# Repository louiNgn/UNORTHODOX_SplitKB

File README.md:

# UNORTHOD0X SPLIT KEYBOARD 
## a "re-staggered" split ortholinear keyboard in between a 65% and a 75% keyboard utilizing usb-c interconnect

A cursed keyboard design that appreciates well-tuned stabilizers and keycap label compatibility while giving a bit of a damn about ergonomics and the well-being of your hands was the reason why this project was created. 

FIRMWARE IS TO BE ADDED ONCE I GET MY HANDS ON THE KEYBOARD, AS I DO NOT HAVE EXPERIENCE WITH DEVVING PI PICO INTERCONNECT!

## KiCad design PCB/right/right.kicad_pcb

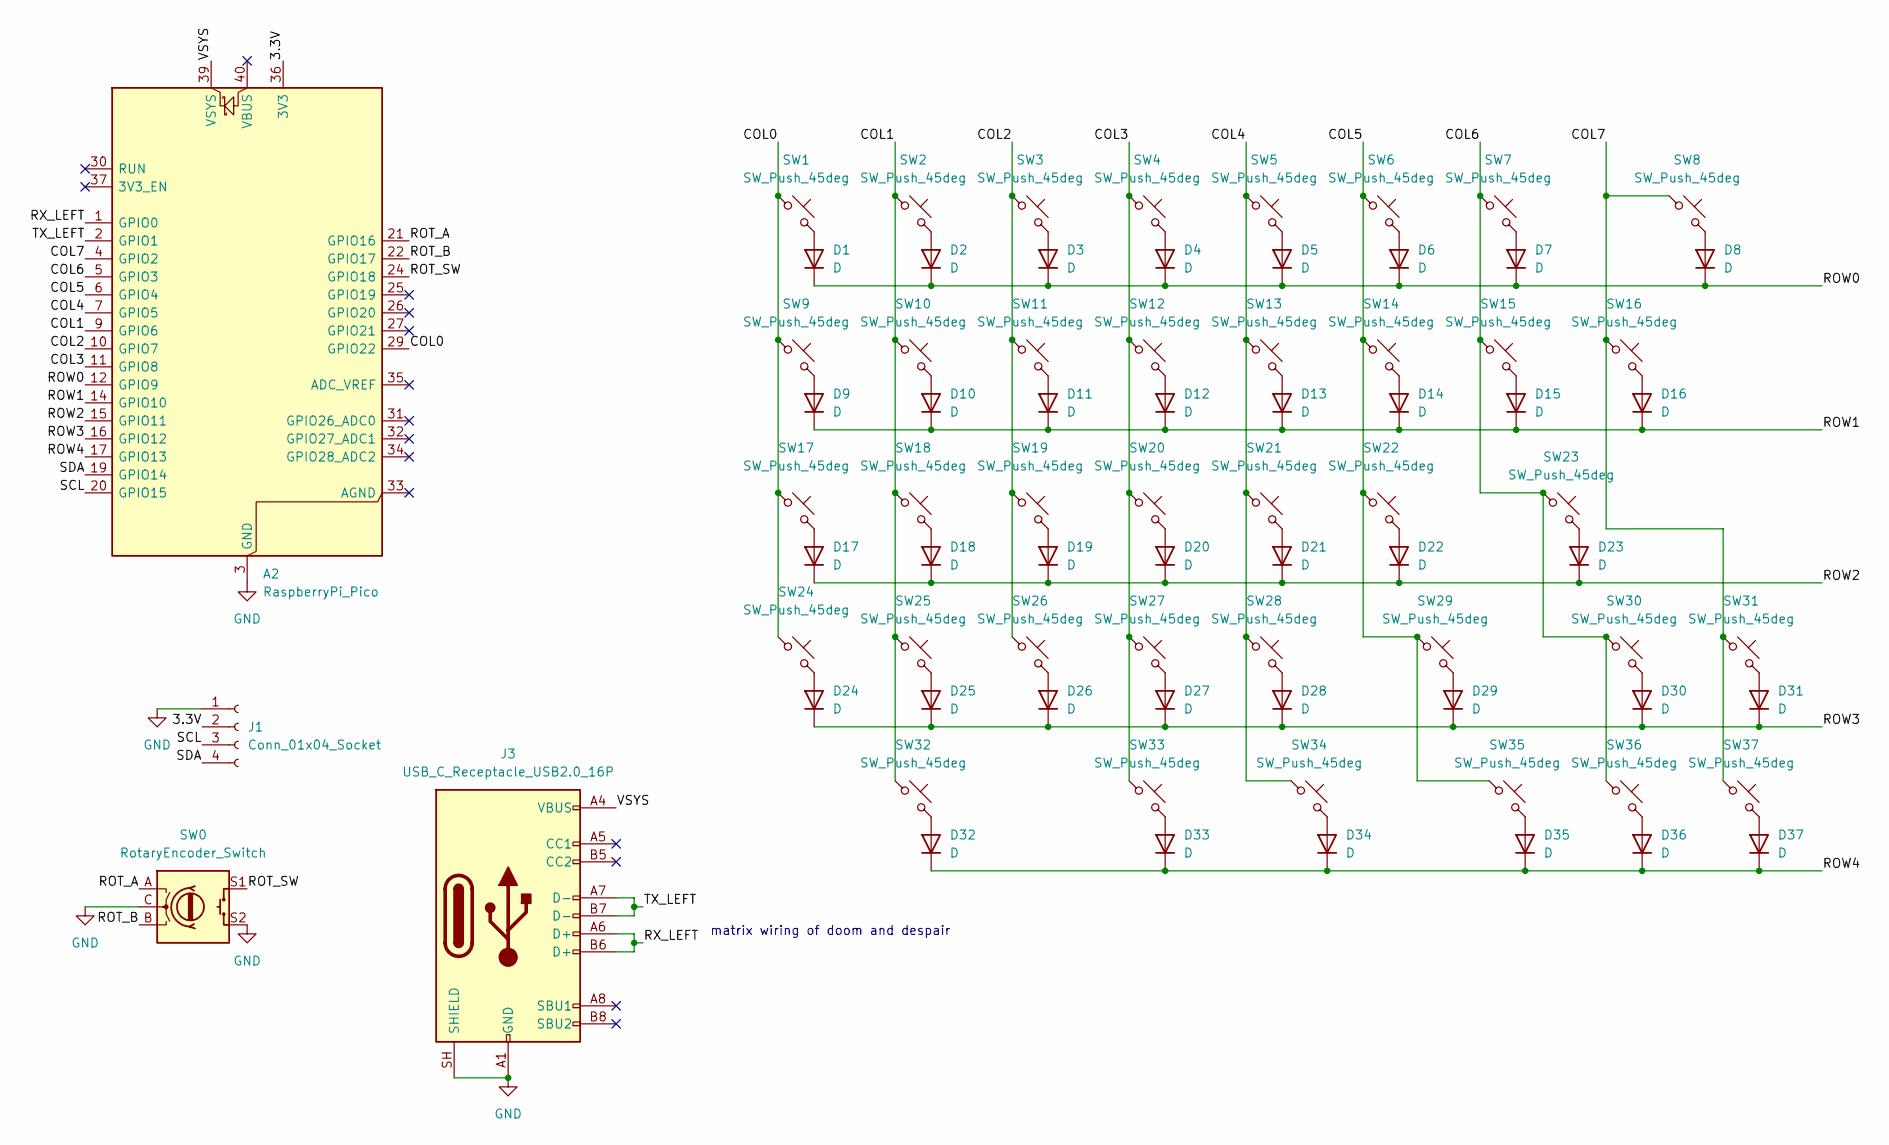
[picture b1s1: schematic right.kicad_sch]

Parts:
A2: RaspberryPi_Pico; RaspberryPi_Pico_Common_THT
D1, D2, D3, D4, D5, D6, D7, D8, D9, D10, D11, D12, D13, D14, D15, D16, D17, D18, D19, D20, D21, D22, D23, D24, D25, D26, D27, D28, D29, D30, D31, D32, D33, D34, D35, D36, D37: D; D_SOD-123
J1: Conn_01x04_Socket; ER_OLEDM0.91_1x-I2C
J3: USB_C_Receptacle_USB2.0_16P; USB_C_Receptacle_HCTL_HC-TYPE-C-16P-01A
SW0: RotaryEncoder_Switch; ROT_Alps_EC11E-Switch
SW1, SW2, SW3, SW4, SW5, SW6, SW7, SW9, SW10, SW11, SW12, SW13, SW14, SW15, SW17, SW18, SW19, SW20, SW21, SW22, SW24, SW25, SW26, SW27, SW28, SW30, SW31, SW35, SW36, SW37: SW_Push_45deg; SW_Hotswap_Kailh_MX_Plated_1.00u
SW8, SW16: SW_Push_45deg; SW_Hotswap_Kailh_MX_Plated_2.00u
SW23, SW32: SW_Push_45deg; SW_Hotswap_Kailh_MX_Plated_2.75u
SW29: SW_Push_45deg; SW_Hotswap_Kailh_MX_Plated_2.25u
SW33, SW34: SW_Push_45deg; SW_Hotswap_Kailh_MX_Plated_1.50u

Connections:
/3.3V: A2.36 (3V3), J1.2
/COL0: A2.29 (GPIO22), SW1.1, SW9.1, SW17.1, SW24.1
/COL1: A2.9 (GPIO6), SW2.1, SW10.1, SW18.1, SW25.1, SW32.1
/COL2: A2.10 (GPIO7), SW3.1, SW11.1, SW19.1, SW26.1
/COL3: A2.11 (GPIO8), SW4.1, SW12.1, SW20.1, SW27.1, SW33.1
/COL4: A2.7 (GPIO5), SW5.1, SW13.1, SW21.1, SW28.1, SW34.1
/COL5: A2.6 (GPIO4), SW6.1, SW14.1, SW22.1, SW29.1, SW35.1
/COL6: A2.5 (GPIO3), SW7.1, SW15.1, SW23.1, SW30.1, SW36.1
/COL7: A2.4 (GPIO2), SW8.1, SW16.1, SW31.1, SW37.1
/ROT_A: A2.21 (GPIO16), SW0.A
/ROT_B: A2.22 (GPIO17), SW0.B
/ROT_SW: A2.24 (GPIO18), SW0.S1
/ROW0: A2.12 (GPIO9), D1.1 (K), D2.1 (K), D3.1 (K), D4.1 (K), D5.1 (K), D6.1 (K), D7.1 (K), D8.1 (K)
/ROW1: A2.14 (GPIO10), D9.1 (K), D10.1 (K), D11.1 (K), D12.1 (K), D13.1 (K), D14.1 (K), D15.1 (K), D16.1 (K)
/ROW2: A2.15 (GPIO11), D17.1 (K), D18.1 (K), D19.1 (K), D20.1 (K), D21.1 (K), D22.1 (K), D23.1 (K)
/ROW3: A2.16 (GPIO12), D24.1 (K), D25.1 (K), D26.1 (K), D27.1 (K), D28.1 (K), D29.1 (K), D30.1 (K), D31.1 (K)
/ROW4: A2.17 (GPIO13), D32.1 (K), D33.1 (K), D34.1 (K), D35.1 (K), D36.1 (K), D37.1 (K)
/RX_LEFT: A2.1 (GPIO0), J3.A6 (D+), J3.B6 (D+)
/SCL: A2.20 (GPIO15), J1.3
/SDA: A2.19 (GPIO14), J1.4
/TX_LEFT: A2.2 (GPIO1), J3.A7 (D-), J3.B7 (D-)
/VSYS: A2.39 (VSYS), J3.A4 (VBUS), J3.A9 (VBUS), J3.B4 (VBUS), J3.B9 (VBUS)
GND: A2.3 (GND), A2.8 (GND), A2.13 (GND), A2.18 (GND), A2.23 (GND), A2.28 (GND), A2.38 (GND), J1.1, J3.A1 (GND), J3.A12 (GND), J3.B1 (GND), J3.B12 (GND), J3.SH (SHIELD), SW0.C, SW0.S2
unnamed: D1.2 (A), SW1.2
unnamed: D2.2 (A), SW2.2
unnamed: D3.2 (A), SW3.2
unnamed: D4.2 (A), SW4.2
unnamed: D5.2 (A), SW5.2
unnamed: D6.2 (A), SW6.2
unnamed: D7.2 (A), SW7.2
unnamed: D8.2 (A), SW8.2
unnamed: D9.2 (A), SW9.2
unnamed: D10.2 (A), SW10.2
unnamed: D11.2 (A), SW11.2
unnamed: D12.2 (A), SW12.2
unnamed: D13.2 (A), SW13.2
unnamed: D14.2 (A), SW14.2
unnamed: D15.2 (A), SW15.2
unnamed: D16.2 (A), SW16.2
unnamed: D17.2 (A), SW17.2
unnamed: D18.2 (A), SW18.2
unnamed: D19.2 (A), SW19.2
unnamed: D20.2 (A), SW20.2
unnamed: D21.2 (A), SW21.2
unnamed: D22.2 (A), SW22.2
unnamed: D23.2 (A), SW23.2
unnamed: D24.2 (A), SW24.2
unnamed: D25.2 (A), SW25.2
unnamed: D26.2 (A), SW26.2
unnamed: D27.2 (A), SW27.2
unnamed: D28.2 (A), SW28.2
unnamed: D29.2 (A), SW29.2
unnamed: D30.2 (A), SW30.2
unnamed: D31.2 (A), SW31.2
unnamed: D32.2 (A), SW32.2
unnamed: D33.2 (A), SW33.2
unnamed: D34.2 (A), SW34.2
unnamed: D35.2 (A), SW35.2
unnamed: D36.2 (A), SW36.2
unnamed: D37.2 (A), SW37.2

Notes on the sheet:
matrix wiring of doom and despair

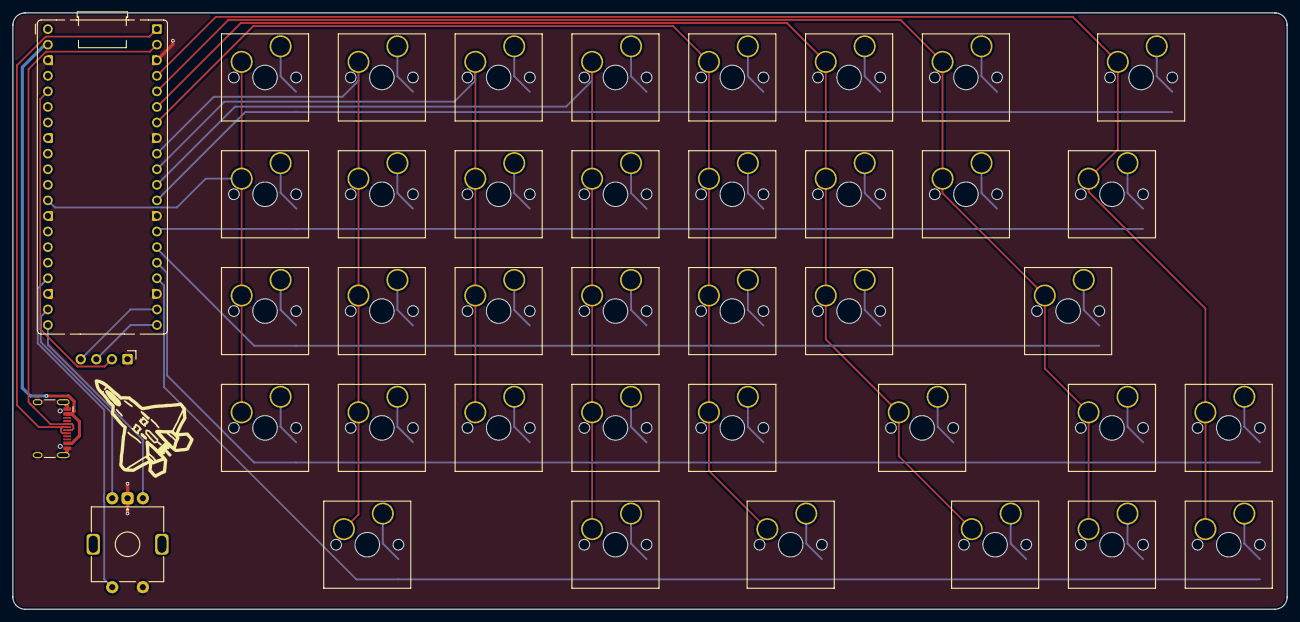
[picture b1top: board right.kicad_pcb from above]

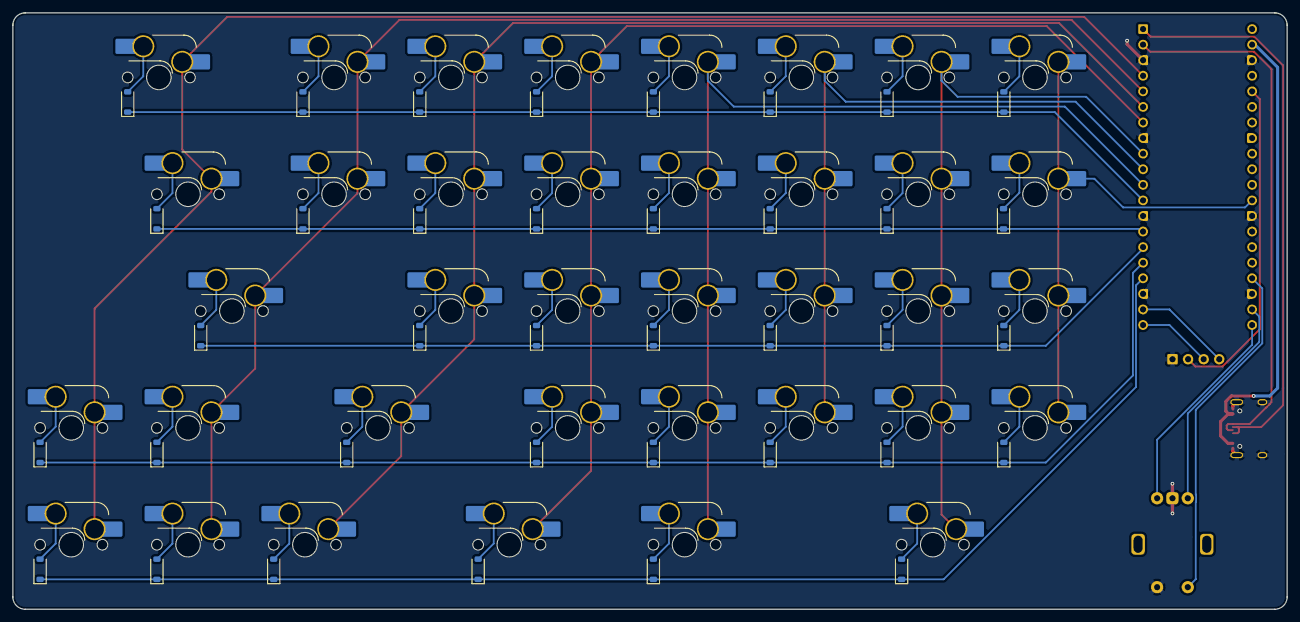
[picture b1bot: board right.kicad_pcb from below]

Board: 2 copper layers, 207.8 x 97.2 mm, 78 parts (38 on the bottom side), 60 nets.
